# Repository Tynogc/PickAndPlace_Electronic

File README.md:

# PickAndPlace_Electronic
The Electronic-Side of an automatic SMT Pick&amp;Place-System

Programm: KiCad

Leiterplatten und embedded-Software für den Pick&Place Automaten

zur Verwendung dieses Repos sind noch die folgenden Repositorys nötig:
https://github.com/Virtex7/PhilippsKicadBauteile
https://github.com/ep092/library_toni.pretty

Diese enthalten KiCAD-Bauteile und Schaltplansymbole

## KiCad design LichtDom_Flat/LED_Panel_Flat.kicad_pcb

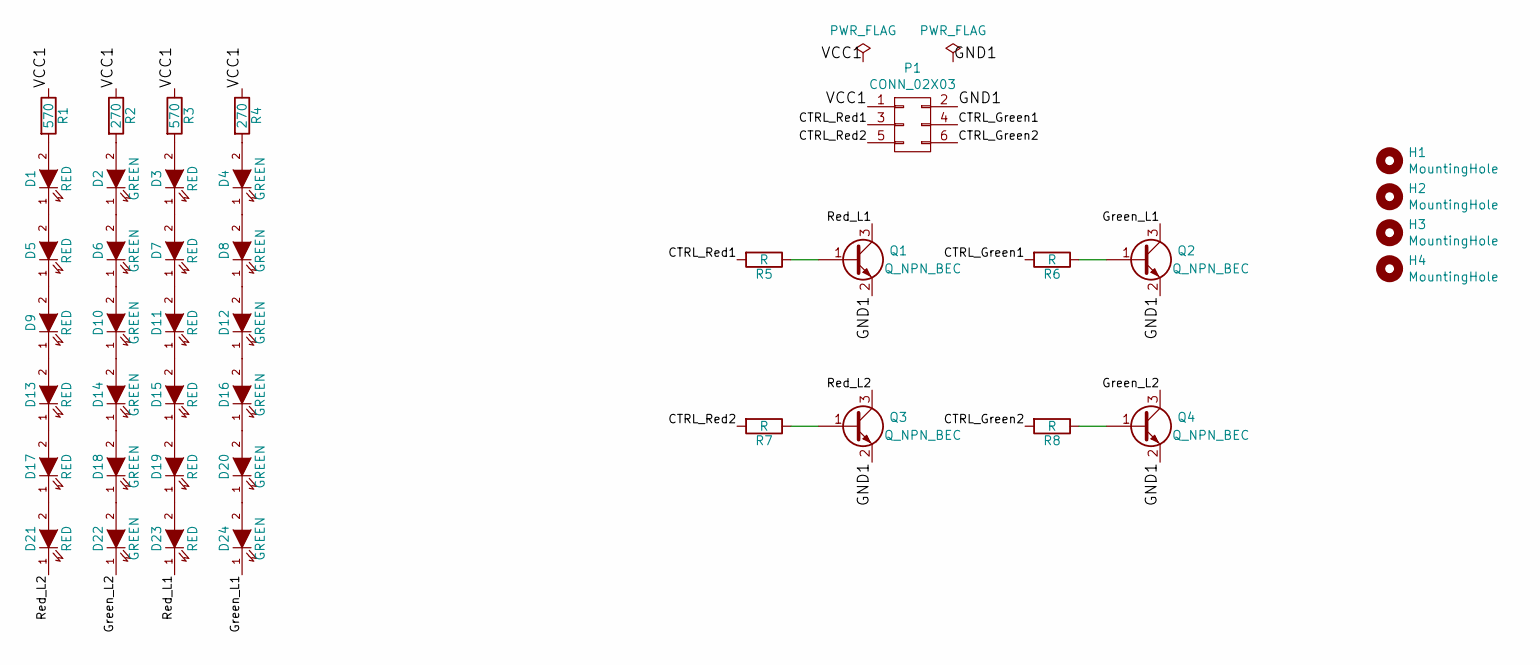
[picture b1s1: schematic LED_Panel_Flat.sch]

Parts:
D1, D3, D5, D7, D9, D11, D13, D15, D17, D19, D21, D23: RED; LED_PLCC-2
D2, D4, D6, D8, D10, D12, D14, D16, D18, D20, D22, D24: GREEN; LED_PLCC-2
H1, H2, H3, H4: MountingHole; MountingHole_3.2mm_M3_DIN965_Pad
P1: CONN_02X03; micro_match3x2
Q1, Q2, Q3, Q4: Q_NPN_BEC; SOT-23
R1, R3: 570; R_1206
R2, R4: 270; R_0805
R5, R6, R7, R8: R; R_0805

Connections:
/CTRL_Green1: P1.4, R6.2
/CTRL_Green2: P1.6, R8.2
/CTRL_Red1: P1.3, R5.2
/CTRL_Red2: P1.5, R7.2
/GND1: P1.2, Q1.2 (E), Q2.2 (E), Q3.2 (E), Q4.2 (E)
/Green_L1: D24.1 (K), Q2.3 (C)
/Green_L2: D22.1 (K), Q4.3 (C)
/Red_L1: D23.1 (K), Q1.3 (C)
/Red_L2: D21.1 (K), Q3.3 (C)
/VCC1: P1.1, R1.1, R2.1, R3.1, R4.1
unnamed: D1.2 (A), R1.2
unnamed: D2.2 (A), R2.2
unnamed: D3.2 (A), R3.2
unnamed: D4.2 (A), R4.2
unnamed: D5.1 (K), D9.2 (A)
unnamed: D1.1 (K), D5.2 (A)
unnamed: D6.1 (K), D10.2 (A)
unnamed: D2.1 (K), D6.2 (A)
unnamed: D7.1 (K), D11.2 (A)
unnamed: D3.1 (K), D7.2 (A)
unnamed: D8.1 (K), D12.2 (A)
unnamed: D4.1 (K), D8.2 (A)
unnamed: D9.1 (K), D13.2 (A)
unnamed: D10.1 (K), D14.2 (A)
unnamed: D11.1 (K), D15.2 (A)
unnamed: D12.1 (K), D16.2 (A)
unnamed: D13.1 (K), D17.2 (A)
unnamed: D14.1 (K), D18.2 (A)
unnamed: D15.1 (K), D19.2 (A)
unnamed: D16.1 (K), D20.2 (A)
unnamed: D17.1 (K), D21.2 (A)
unnamed: D18.1 (K), D22.2 (A)
unnamed: D19.1 (K), D23.2 (A)
unnamed: D20.1 (K), D24.2 (A)
unnamed: Q1.1 (B), R5.1
unnamed: Q2.1 (B), R6.1
unnamed: Q3.1 (B), R7.1
unnamed: Q4.1 (B), R8.1

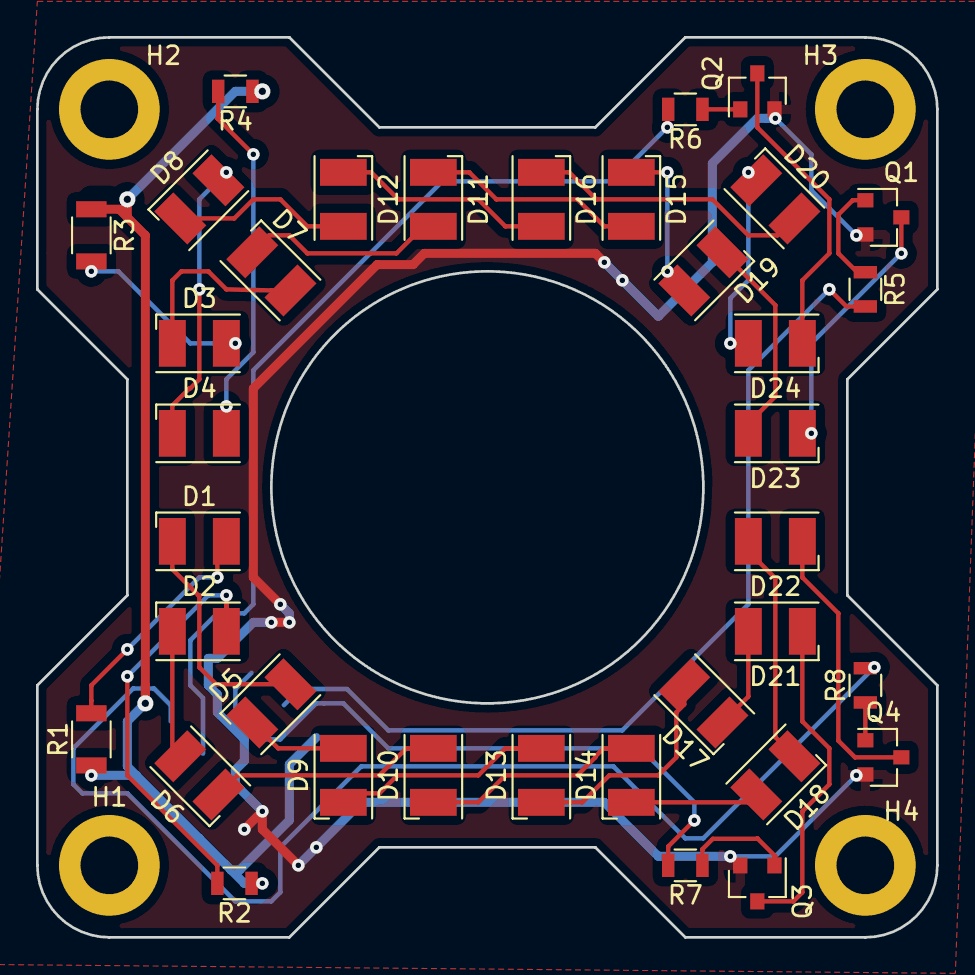
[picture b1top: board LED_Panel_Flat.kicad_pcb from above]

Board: 2 copper layers, 50.0 x 50.0 mm, 41 parts (1 on the bottom side), 38 nets.

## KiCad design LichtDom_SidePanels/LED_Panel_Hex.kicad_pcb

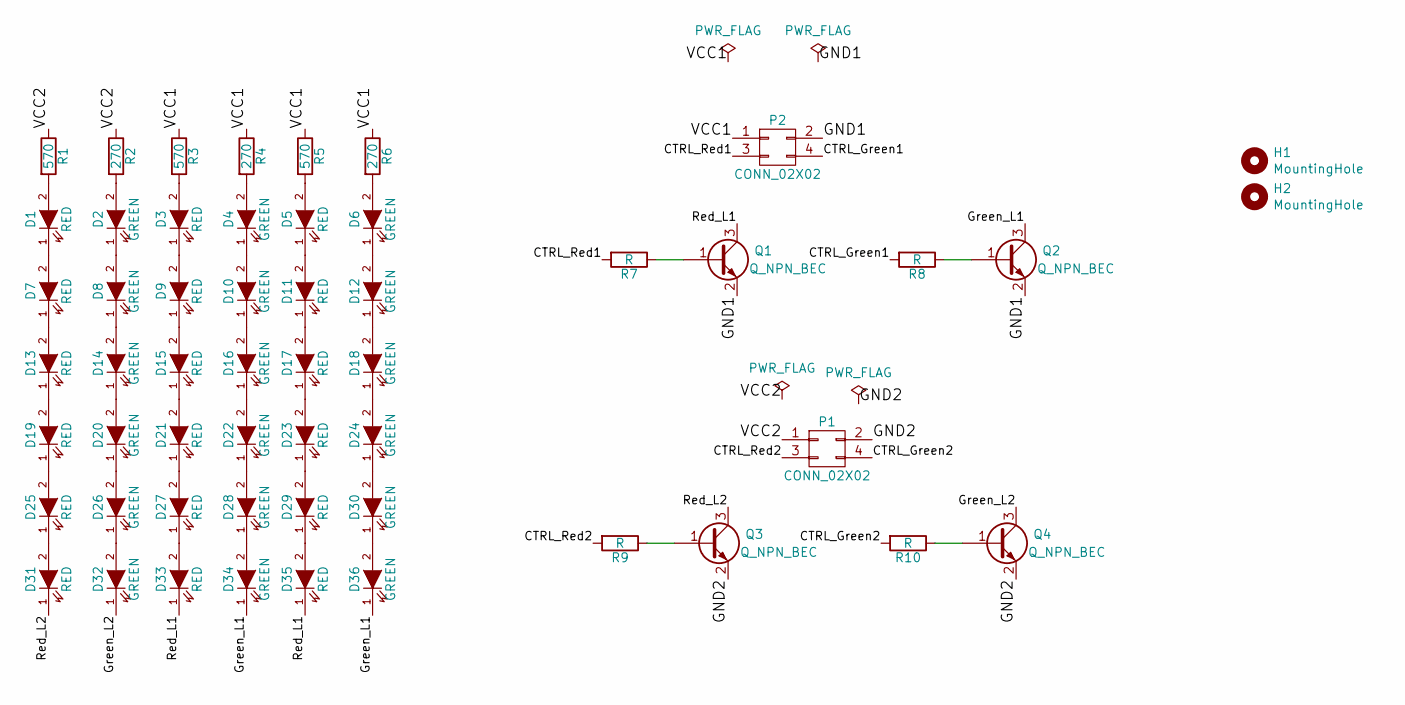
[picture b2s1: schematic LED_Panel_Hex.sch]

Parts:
D1, D3, D5, D7, D9, D11, D13, D15, D17, D19, D21, D23, D25, D27, D29, D31, D33, D35: RED; LED_PLCC-2
D2, D4, D6, D8, D10, D12, D14, D16, D18, D20, D22, D24, D26, D28, D30, D32, D34, D36: GREEN; LED_PLCC-2
H1, H2: MountingHole; MountingHole_3.2mm_M3_DIN965_Pad
P1, P2: CONN_02X02; micro_match3x2
Q1, Q2, Q3, Q4: Q_NPN_BEC; SOT-23
R1, R3, R5: 570; R_1206
R2, R4, R6: 270; R_0805
R7, R8, R9, R10: R; R_0805

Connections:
/CTRL_Green1: P2.4, R8.2
/CTRL_Green2: P1.4, R10.2
/CTRL_Red1: P2.3, R7.2
/CTRL_Red2: P1.3, R9.2
/GND1: P2.2, Q1.2 (E), Q2.2 (E)
/GND2: P1.2, Q3.2 (E), Q4.2 (E)
/Green_L1: D34.1 (K), D36.1 (K), Q2.3 (C)
/Green_L2: D32.1 (K), Q4.3 (C)
/Red_L1: D33.1 (K), D35.1 (K), Q1.3 (C)
/Red_L2: D31.1 (K), Q3.3 (C)
/VCC1: P2.1, R3.1, R4.1, R5.1, R6.1
/VCC2: P1.1, R1.1, R2.1
unnamed: D1.1 (K), D7.2 (A)
unnamed: D1.2 (A), R1.2
unnamed: D2.1 (K), D8.2 (A)
unnamed: D2.2 (A), R2.2
unnamed: D3.1 (K), D9.2 (A)
unnamed: D3.2 (A), R3.2
unnamed: D4.2 (A), R4.2
unnamed: D5.2 (A), R5.2
unnamed: D6.2 (A), R6.2
unnamed: D10.1 (K), D16.2 (A)
unnamed: D4.1 (K), D10.2 (A)
unnamed: D11.1 (K), D17.2 (A)
unnamed: D5.1 (K), D11.2 (A)
unnamed: D12.1 (K), D18.2 (A)
unnamed: D6.1 (K), D12.2 (A)
unnamed: D13.1 (K), D19.2 (A)
unnamed: D7.1 (K), D13.2 (A)
unnamed: D14.1 (K), D20.2 (A)
unnamed: D8.1 (K), D14.2 (A)
unnamed: D15.1 (K), D21.2 (A)
unnamed: D9.1 (K), D15.2 (A)
unnamed: D16.1 (K), D22.2 (A)
unnamed: D17.1 (K), D23.2 (A)
unnamed: D18.1 (K), D24.2 (A)
unnamed: D19.1 (K), D25.2 (A)
unnamed: D20.1 (K), D26.2 (A)
unnamed: D21.1 (K), D27.2 (A)
unnamed: D22.1 (K), D28.2 (A)
unnamed: D23.1 (K), D29.2 (A)
unnamed: D24.1 (K), D30.2 (A)
unnamed: D25.1 (K), D31.2 (A)
unnamed: D26.1 (K), D32.2 (A)
unnamed: D27.1 (K), D33.2 (A)
unnamed: D28.1 (K), D34.2 (A)
unnamed: D29.1 (K), D35.2 (A)
unnamed: D30.1 (K), D36.2 (A)
unnamed: Q1.1 (B), R7.1
unnamed: Q2.1 (B), R8.1
unnamed: Q3.1 (B), R9.1
unnamed: Q4.1 (B), R10.1

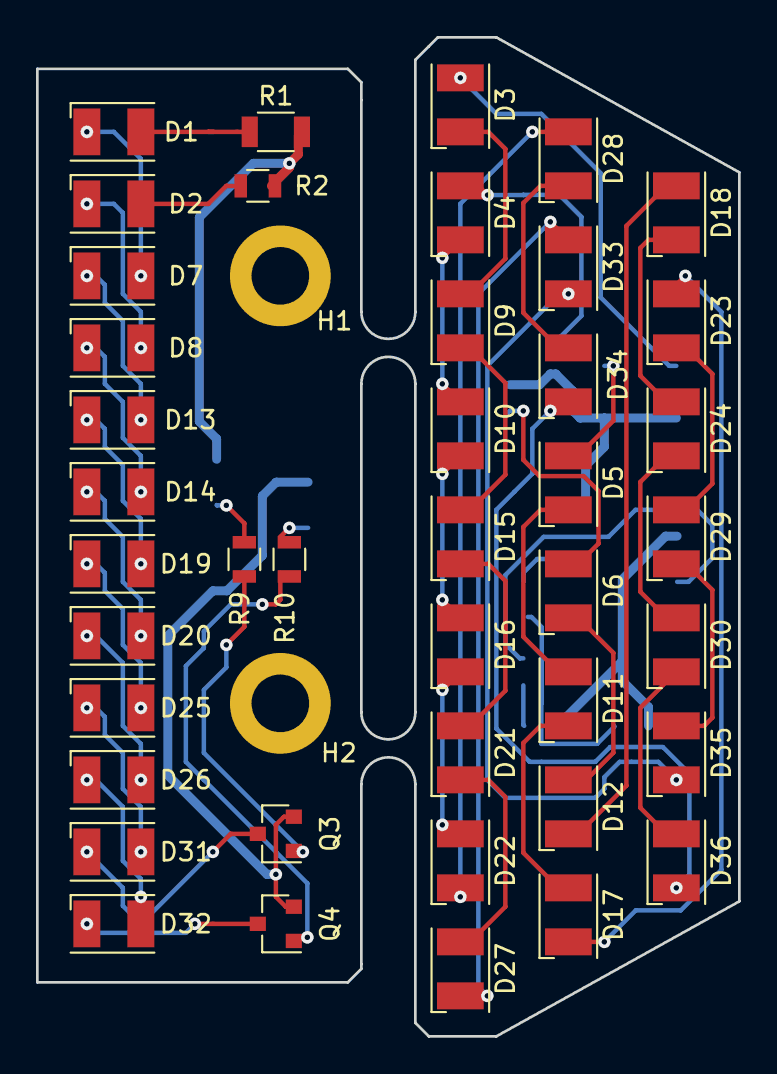
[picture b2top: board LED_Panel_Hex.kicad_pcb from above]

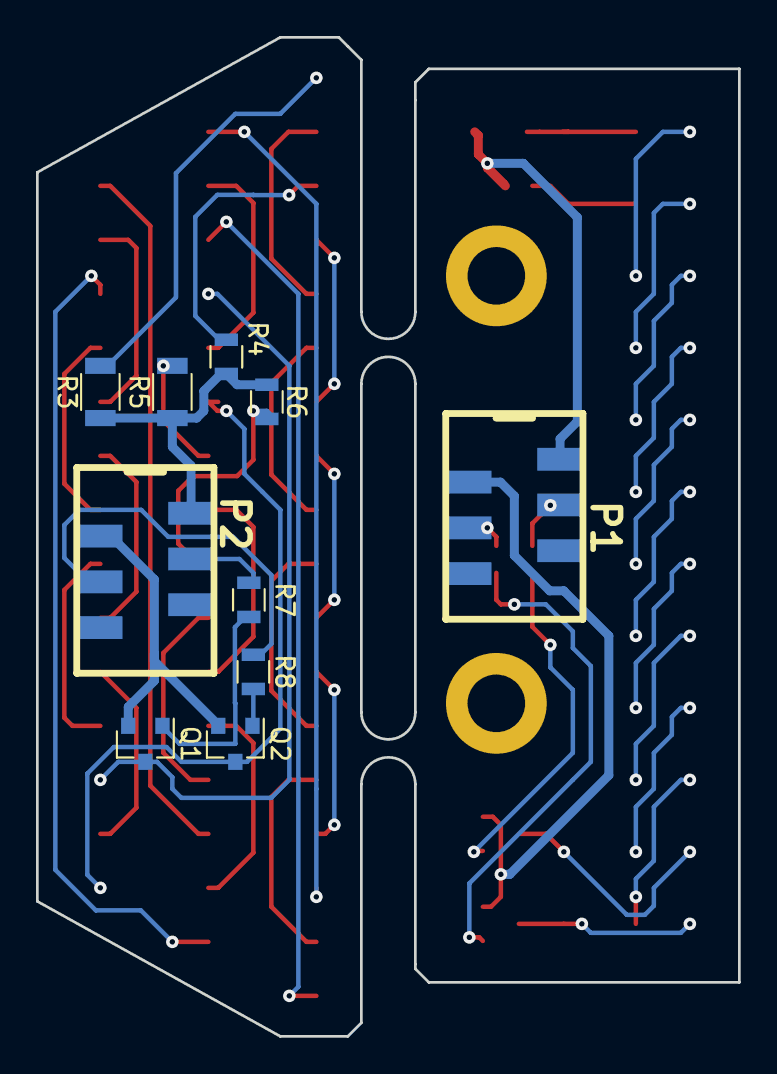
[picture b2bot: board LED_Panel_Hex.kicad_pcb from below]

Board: 2 copper layers, 39.0 x 55.5 mm, 54 parts (10 on the bottom side), 52 nets.

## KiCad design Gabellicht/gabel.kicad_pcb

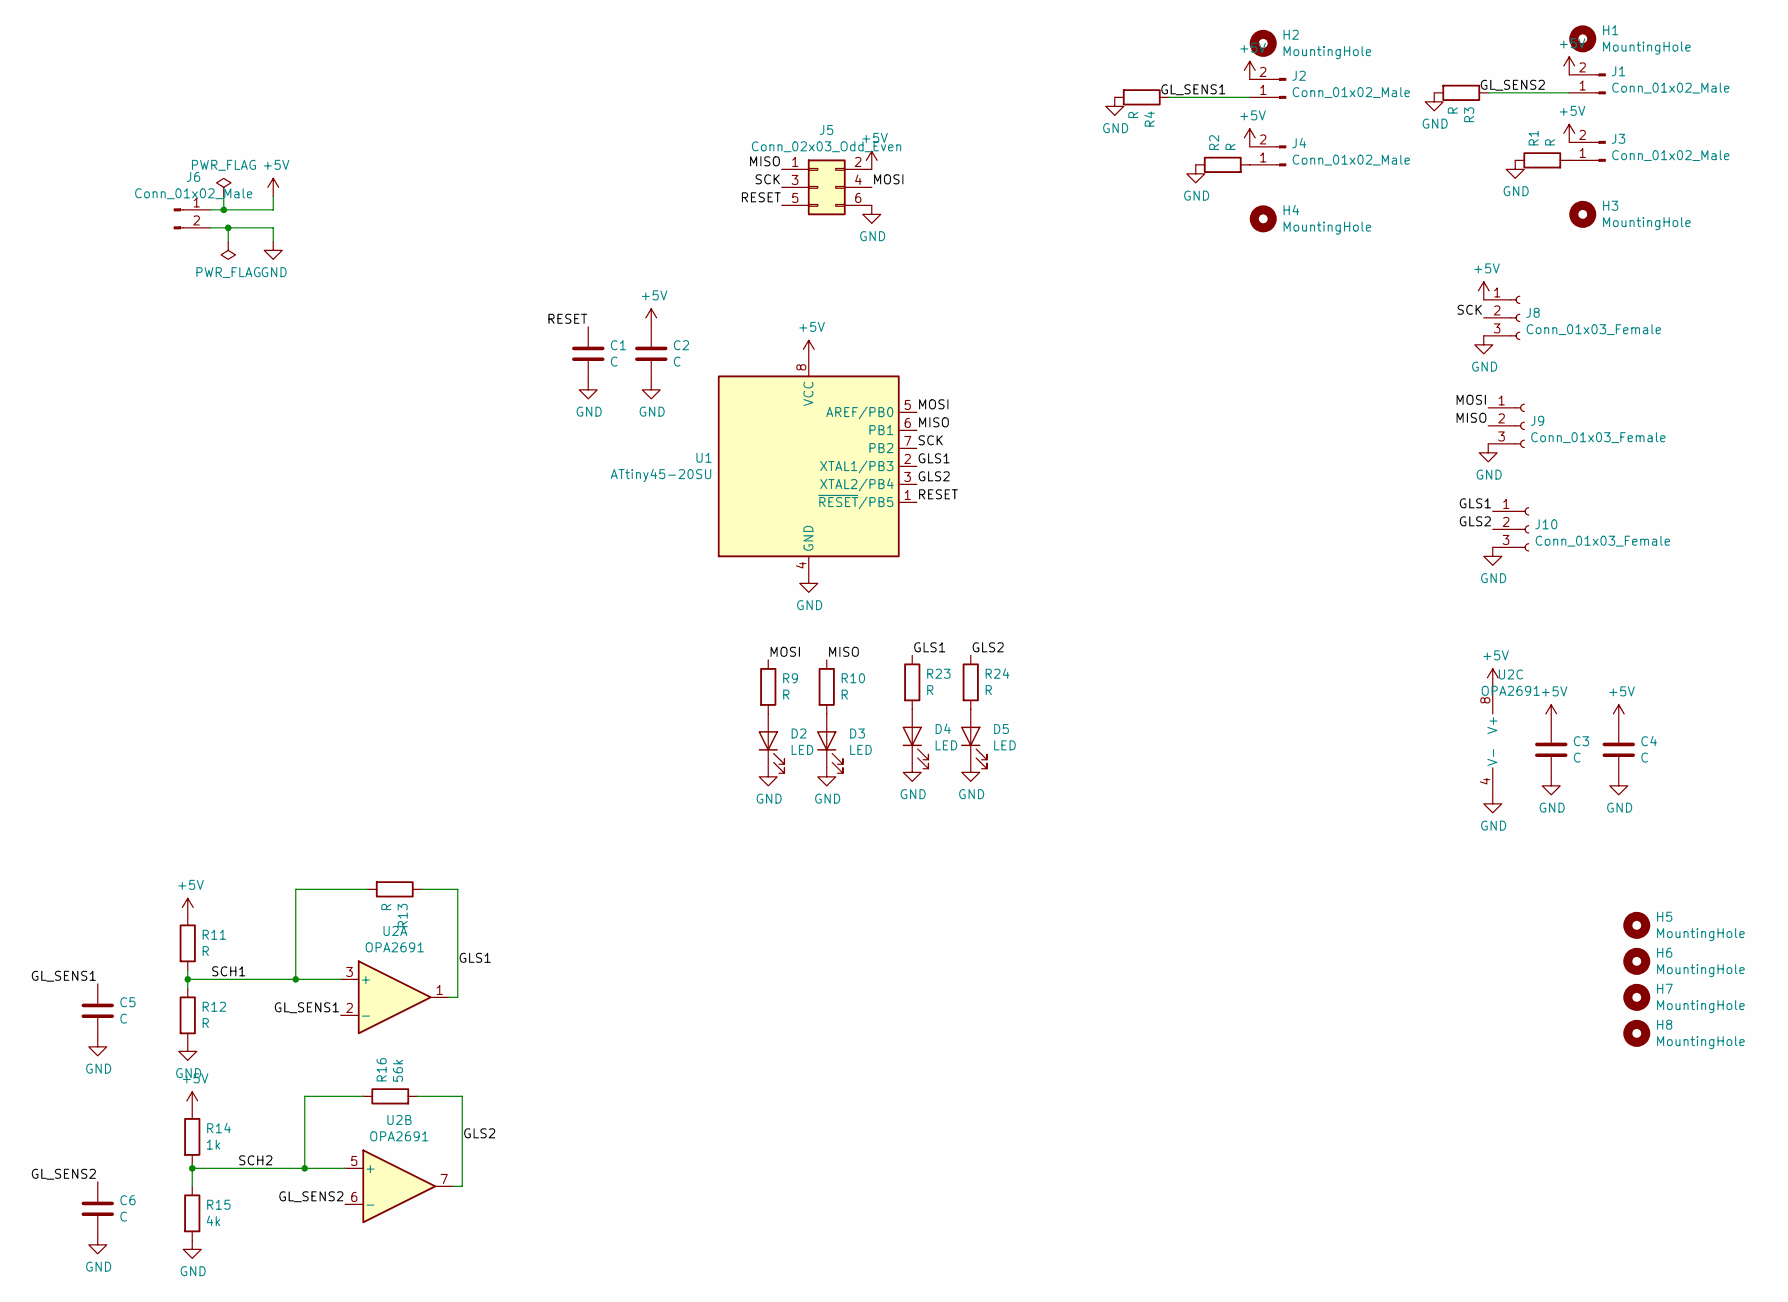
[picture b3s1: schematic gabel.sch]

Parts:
C1, C2, C3, C5, C6: C; C_0805
C4: C; C_1812
D2, D3: LED; LED_0805
D4, D5: LED; LED_D3.0mm_FlatTop
H1, H2, H3, H4: MountingHole; MountingHole_3.2mm_M3_DIN965_Pad
H5, H6, H7, H8: MountingHole; MountingHole_3.2mm_M3
J1, J2, J3, J4, J6: Conn_01x02_Male; Socket_Strip_Straight_1x02_Pitch2.54mm
J5: Conn_02x03_Odd_Even; Socket_Strip_Straight_2x03_Pitch2.54mm
J8, J9, J10: Conn_01x03_Female; Socket_Strip_Straight_1x03_Pitch2.54mm
R1, R2, R3, R4, R9, R10, R11, R12, R13, R23, R24: R; R_0805
R14: 1k; R_0805
R15: 4k; R_0805
R16: 56k; R_0805
U1: ATtiny45-20SU; TI_SO-PowerPAD-8
U2: OPA2691; TI_SO-PowerPAD-8

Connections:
+5V: C2.1, C3.1, C4.1, J1.2, J2.2, J3.2, J4.2, J5.2, J6.1, J8.1, R11.1, R14.1, U1.8 (VCC), U2.8 (V+)
/GLS1: J10.1, R13.1, R23.1, U1.2 (XTAL1/PB3), U2.1
/GLS2: J10.2, R16.2, R24.1, U1.3 (XTAL2/PB4), U2.7
/GL_SENS1: C5.1, J2.1, R4.1, U2.2 (-)
/GL_SENS2: C6.1, J1.1, R3.1, U2.6 (-)
/MISO: J5.1, J9.2, R10.1, U1.6 (PB1)
/MOSI: J5.4, J9.1, R9.1, U1.5 (AREF/PB0)
/RESET: C1.1, J5.5, U1.1 (~RESET~/PB5)
/SCH1: R11.2, R12.1, R13.2, U2.3 (+)
/SCH2: R14.2, R15.1, R16.1, U2.5 (+)
/SCK: J5.3, J8.2, U1.7 (PB2)
GND: C1.2, C2.2, C3.2, C4.2, C5.2, C6.2, D2.1 (K), D3.1 (K), D4.1 (K), D5.1 (K), J5.6, J6.2, J8.3, J9.3, J10.3, R1.1, R2.1, R3.2, R4.2, R12.2, R15.2, U1.4 (GND), U2.4 (V-)
unnamed: D2.2 (A), R9.2
unnamed: D3.2 (A), R10.2
unnamed: D4.2 (A), R23.2
unnamed: D5.2 (A), R24.2
unnamed: J3.1, R1.2
unnamed: J4.1, R2.2

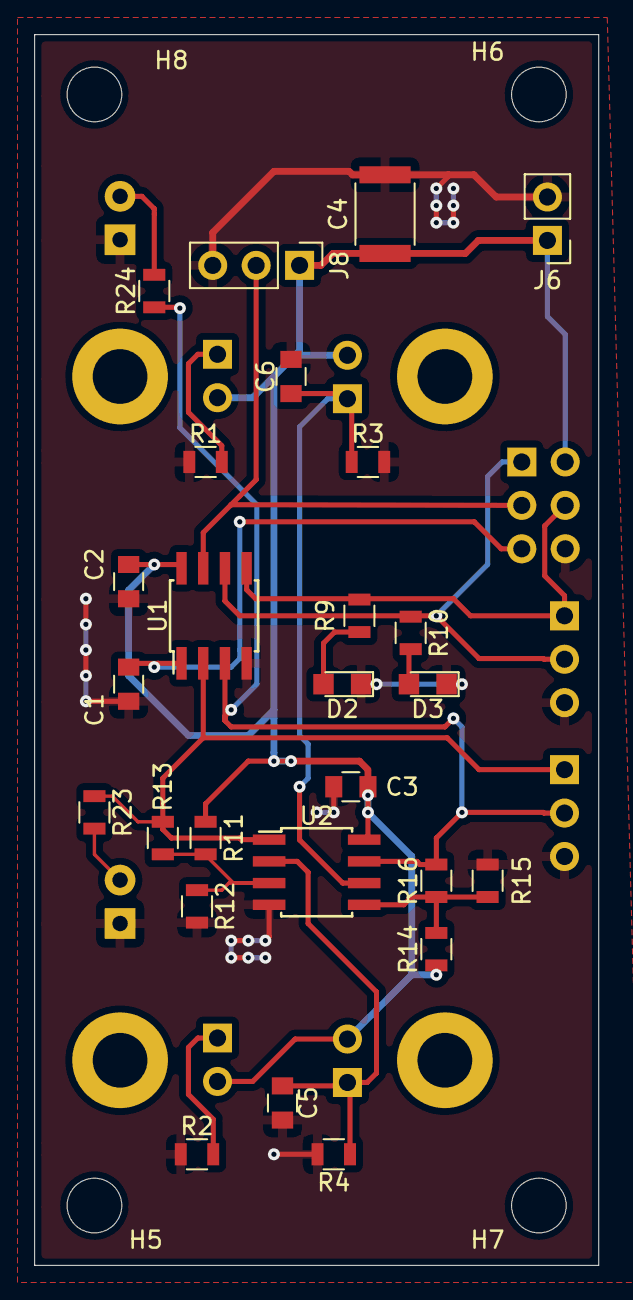
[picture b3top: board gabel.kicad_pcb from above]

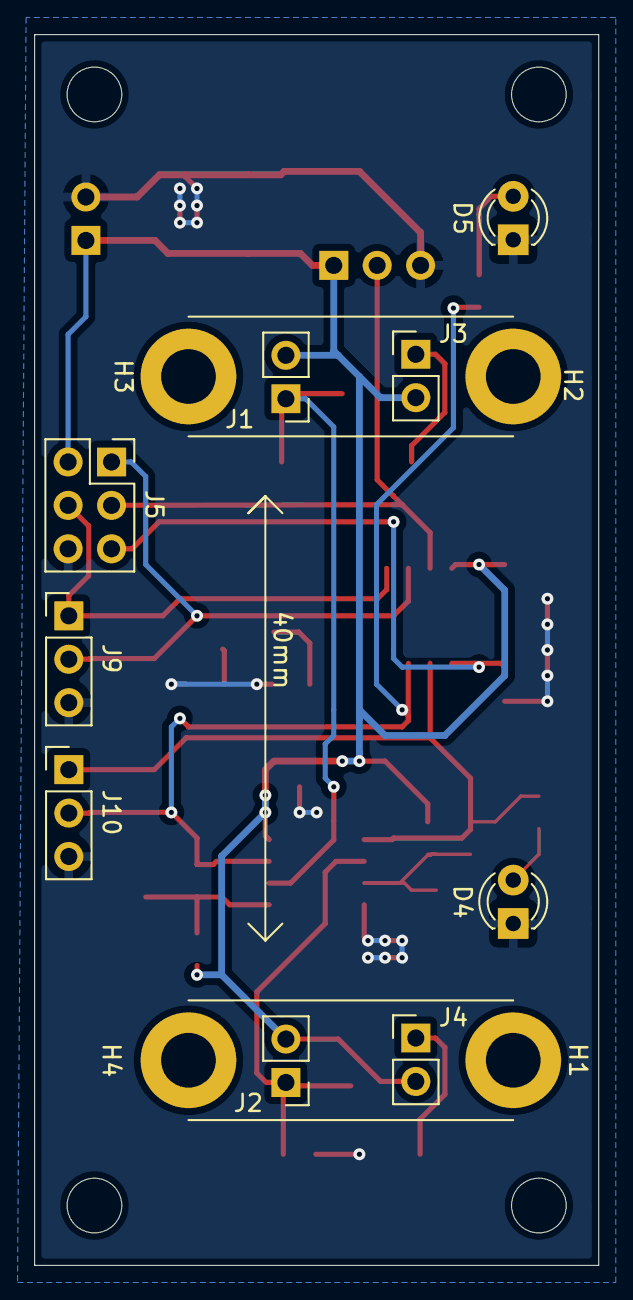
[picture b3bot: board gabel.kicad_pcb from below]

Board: 2 copper layers, 33.0 x 72.0 mm, 43 parts (13 on the bottom side), 18 nets.

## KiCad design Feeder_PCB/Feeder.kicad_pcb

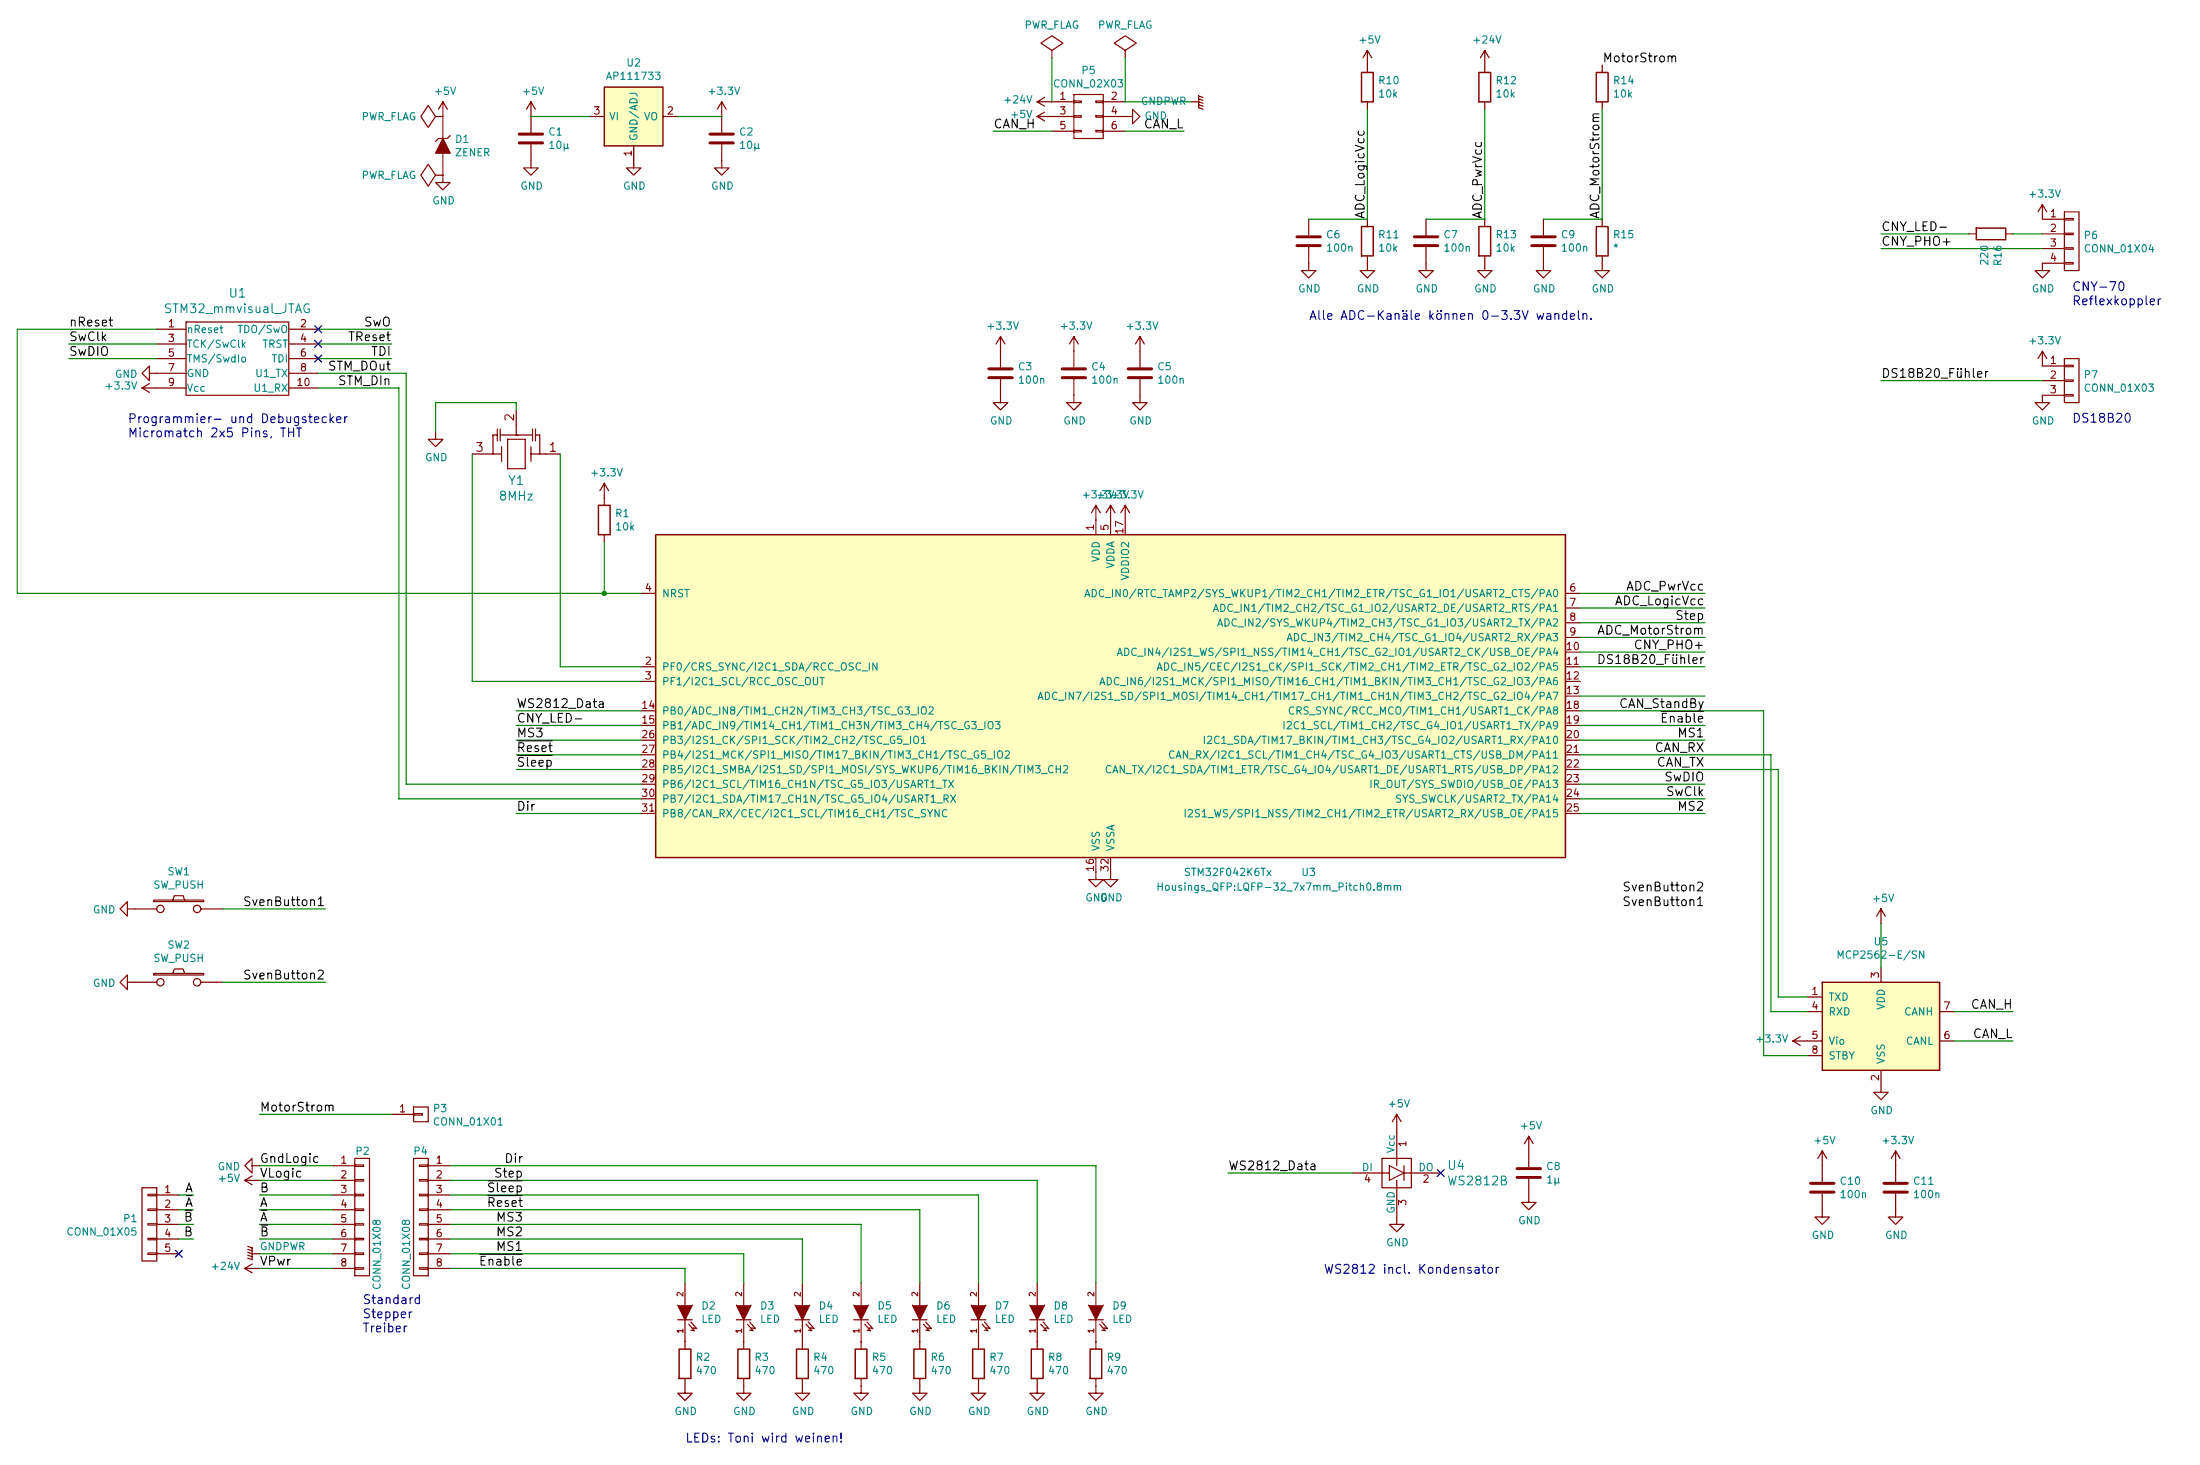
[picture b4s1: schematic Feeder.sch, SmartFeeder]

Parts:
C1, C2: 10µ; C_0805
C3, C4, C5, C6, C7, C9, C10, C11: 100n; C_0603
C8: 1µ; C_0603
D1: ZENER; D_MiniMELF_Standard
D2, D3, D4, D5, D6, D7, D8, D9: LED; LED_0603
P1: CONN_01X05; JST_XH_B05B-XH-A_05x2.50mm_Straight
P2, P4: CONN_01X08; Socket_Strip_Straight_1x08_Pitch2.54mm
P3: CONN_01X01; Pin_Header_Straight_1x01_Pitch2.54mm
P5: CONN_02X03; Pin_Header_Angled_2x03_Pitch2.54mm
P6: CONN_01X04; JST_PH_B4B-PH-K_04x2.00mm_Straight
P7: CONN_01X03; Pin_Header_Straight_1x03_Pitch2.54mm
R1, R10, R11, R12, R13, R14: 10k; R_0603
R2, R3, R4, R5, R6, R7, R8, R9: 470; R_0603
R15: *; R_0603
R16: 220; R_0603
SW1, SW2: SW_PUSH
U1: STM32_mmvisual_JTAG; MICROMATCH-10
U2: AP111733; SOT-223
U3: STM32F042K6Tx; LQFP-32_7x7mm_Pitch0.8mm
U4: WS2812B; LED_WS2812B-PLCC4
U5: MCP2562-E/SN; SOIC-8_3.9x4.9mm_Pitch1.27mm
Y1: 8MHz; CSTCE_3,2x1,3

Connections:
+3V3: C2.1, C3.1, C4.1, C5.1, C11.1, P6.1, P7.1, R1.1, U1.9 (Vcc), U2.2 (VO), U2.4 (VO), U3.1 (VDD), U3.5 (VDDA), U3.17 (VDDIO2), U5.5 (Vio)
+5V: C1.1, C8.1, C10.1, D1.1 (K), P2.2, P5.3, R10.1, U2.3 (VI), U4.1 (Vcc), U5.3 (VDD)
+24V: P2.8, P5.1, R12.1
/A: P1.1, P2.4
/ADC_LogicVcc: C6.1, R10.2, R11.1, U3.7 (ADC_IN1/TIM2_CH2/TSC_G1_IO2/USART2_DE/U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)
/ADC_MotorStrom: C9.1, R14.2, R15.1, U3.9 (ADC_IN3/TIM2_CH4/TSC_G1_IO4/USART2_RX/P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)
/ADC_PwrVcc: C7.1, R12.2, R13.1, U3.6 (ADC_IN0/RTC_TAMP2/SYS_WKUP1/TIM2_CH1/TI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)
/B: P1.4, P2.3
/CAN_H: P5.5, U5.7 (CANH)
/CAN_L: P5.6, U5.6 (CANL)
/CAN_RX: U3.21 (CAN_RX/I2C1_SCL/TIM1_CH4/TSC_G4_IO3/USA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), U5.4 (RXD)
/CAN_StandBy: U3.18 (CRS_SYNC/RCC_MCO/TIM1_CH1/USART1_CK/PA8), U5.8 (STBY)
/CAN_TX: U3.22 (CAN_TX/I2C1_SDA/TIM1_ETR/TSC_G4_IO4/USA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), U5.1 (TXD)
/CNY_LED-: R16.2, U3.15 (PB1/ADC_IN9/TIM14_CH1/TIM1_CH3N/TIM3_CH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)
/CNY_PHO+: P6.3, U3.10 (ADC_IN4/I2S1_WS/SPI1_NSS/TIM14_CH1/TSC_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)
/DS18B20_Fühler: P7.2, U3.11 (ADC_IN5/CEC/I2S1_CK/SPI1_SCK/TIM2_CH1/T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)
/Dir: D9.2 (A), P4.1, U3.31 (PB8/CAN_RX/CEC/I2C1_SCL/TIM16_CH1/TSC_S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)
/MS1: D3.2 (A), P4.7, U3.20 (I2C1_SDA/TIM17_BKIN/TIM1_CH3/TSC_G4_IO2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)
/MS2: D4.2 (A), P4.6, U3.25 (I2S1_WS/SPI1_NSS/TIM2_CH1/TIM2_ETR/USAR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)
/MS3: D5.2 (A), P4.5, U3.26 (PB3/I2S1_CK/SPI1_SCK/TIM2_CH2/TSC_G5_IO1)
/MotorStrom: P3.1, R14.1
/STM_DIn: U1.10 (U1_RX), U3.30 (PB7/I2C1_SDA/TIM17_CH1N/TSC_G5_IO4/USAR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)
/STM_DOut: U1.8 (U1_TX), U3.29 (PB6/I2C1_SCL/TIM16_CH1N/TSC_G5_IO3/USAR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)
/Step: D8.2 (A), P4.2, U3.8 (ADC_IN2/SYS_WKUP4/TIM2_CH3/TSC_G1_IO3/U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)
/SwClk: U1.3 (TCK/SwClk), U3.24 (SYS_SWCLK/USART2_TX/PA14)
/SwDIO: U1.5 (TMS/SwdIo), U3.23 (IR_OUT/SYS_SWDIO/USB_OE/PA13)
/SwO: U1.2 (TDO/SwO)
/TDI: U1.6 (TDI)
/TReset: U1.4 (TRST)
/WS2812_Data: U3.14 (PB0/ADC_IN8/TIM1_CH2N/TIM3_CH3/TSC_G3_I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), U4.4 (DI)
/nReset: R1.2, U1.1 (nReset), U3.4 (NRST)
/~A: P1.2, P2.5
/~B: P1.3, P2.6
/~Enable: D2.2 (A), P4.8, U3.19 (I2C1_SCL/TIM1_CH2/TSC_G4_IO1/USART1_TX/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)
/~Reset: D6.2 (A), P4.4, U3.27 (PB4/I2S1_MCK/SPI1_MISO/TIM17_BKIN/TIM3_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)
/~Sleep: D7.2 (A), P4.3, U3.28 (PB5/I2C1_SMBA/I2S1_SD/SPI1_MOSI/SYS_WKU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)
GND: C1.2, C2.2, C3.2, C4.2, C5.2, C6.2, C7.2, C8.2, C9.2, C10.2, C11.2, D1.2 (A), P2.1, P5.4, P6.4, P7.3, R2.2, R3.2, R4.2, R5.2, R6.2, R7.2, R8.2, R9.2, R11.2, R13.2, R15.2, SW1.1, SW2.1, U1.7 (GND), U2.1 (GND/ADJ), U3.16 (VSS), U3.32 (VSSA), U4.3 (GND), U5.2 (VSS), Y1.2
GNDPWR: P2.7, P5.2
unnamed: D2.1 (K), R2.1
unnamed: D3.1 (K), R3.1
unnamed: D4.1 (K), R4.1
unnamed: D5.1 (K), R5.1
unnamed: D6.1 (K), R6.1
unnamed: D7.1 (K), R7.1
unnamed: D8.1 (K), R8.1
unnamed: D9.1 (K), R9.1
unnamed: P6.2, R16.1
unnamed: U3.2 (PF0/CRS_SYNC/I2C1_SDA/RCC_OSC_IN), Y1.1
unnamed: U3.3 (PF1/I2C1_SCL/RCC_OSC_OUT), Y1.3

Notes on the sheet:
Standard Stepper Treiber
Alle ADC-Kanäle können 0-3.3V wandeln.
Programmier- und Debugstecker Micromatch 2x5 Pins, THT
LEDs: Toni wird weinen!
WS2812 incl. Kondensator
CNY-70 Reflexkoppler
DS18B20

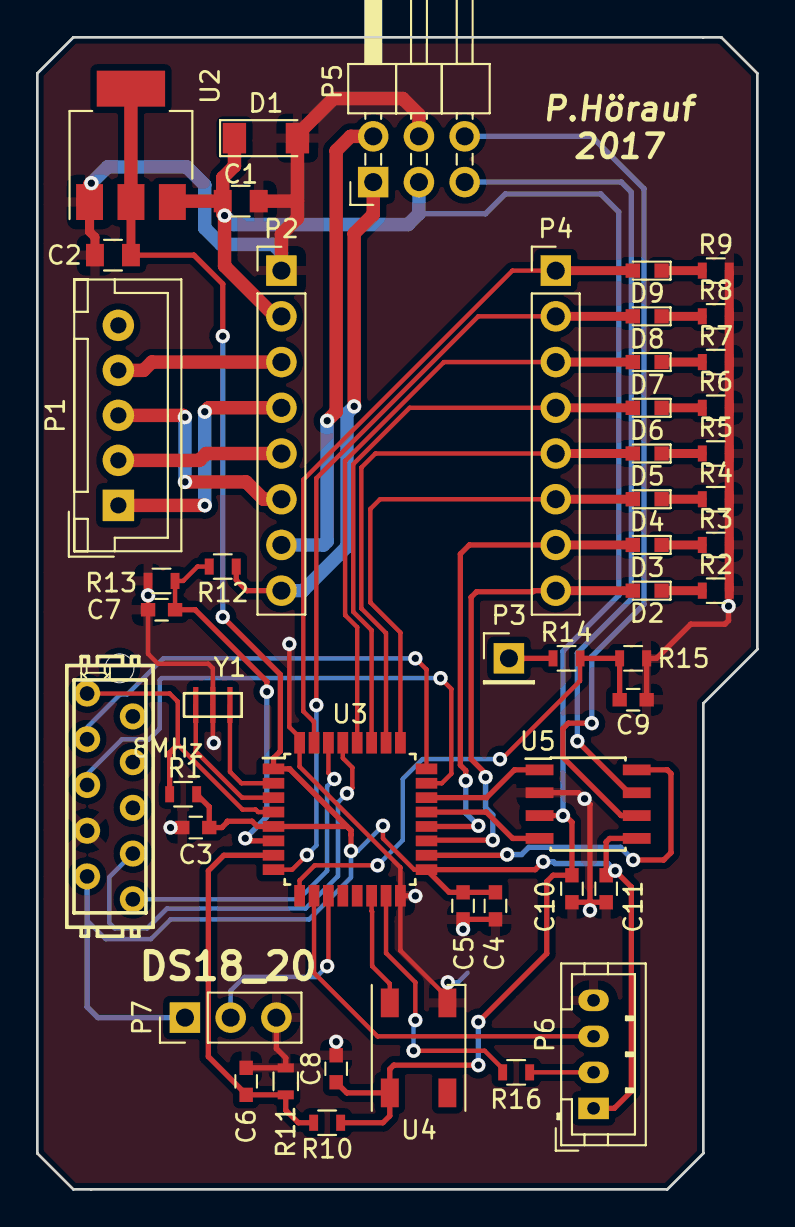
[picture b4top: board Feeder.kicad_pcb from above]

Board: 2 copper layers, 40.0 x 64.0 mm, 49 parts (0 on the bottom side), 46 nets.

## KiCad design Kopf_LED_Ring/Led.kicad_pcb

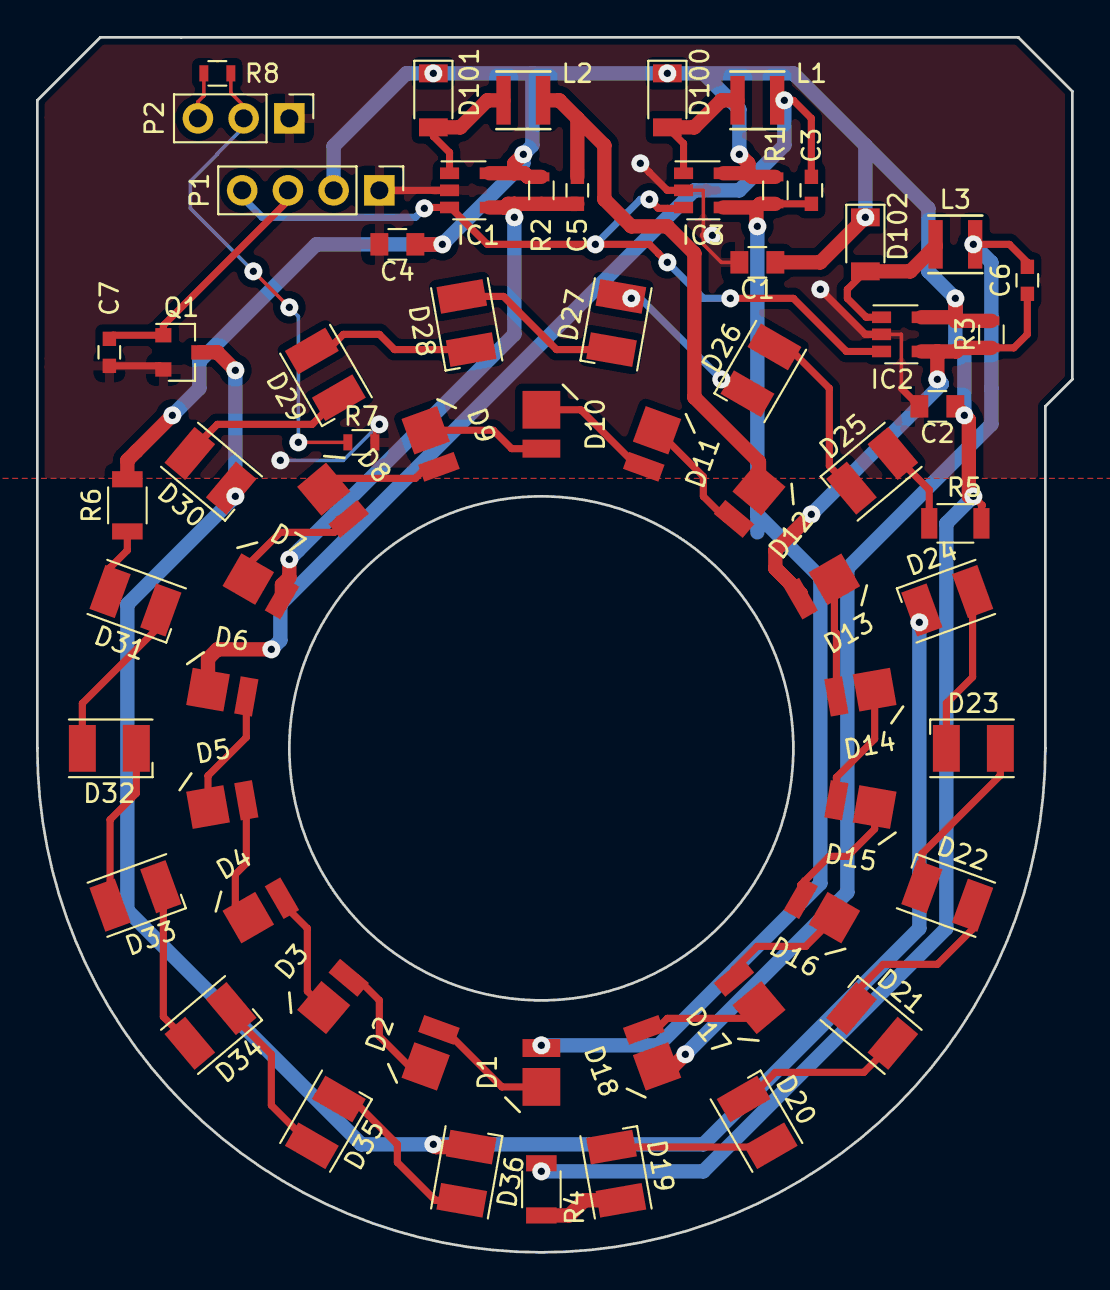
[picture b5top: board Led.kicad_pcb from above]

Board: 2 copper layers, 57.5 x 67.5 mm, 63 parts (0 on the bottom side), 49 nets.

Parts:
C1, C2, C4: 2u2; C_0805
C3, C5, C6, C7: 100n; C_0603
D1, D2, D3, D4, D5, D6, D7, D8, D9, D10, D11, D12, D13, D14, D15, D16, D17, D18: White; PLCC_EAHC2835
D19, D20, D21, D22, D23, D24, D25, D26, D27, D28, D29, D30, D31, D32, D33, D34, D35, D36: RED; LED_PLCC-2
D100, D101, D102: D_Schottky; D_1206
IC1, IC2, IC3: AL8808; SOT-23-5
L1, L2, L3: L; Inductor_Taiyo-Yuden_MD-3030
P1: CONN_01X04; Socket_Strip_Straight_1x04_Pitch2.54mm
P2: CONN_01X03; Socket_Strip_Straight_1x03_Pitch2.54mm
Q1: Q_NMOS_GSD; SOT-23
R1, R2, R3: 1R 1%; R_0603
R4, R5, R6: R; R_1206
R7: TempSens; R_0603
R8: R; R_0603

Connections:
+24V: C1.1, C2.1, C4.1, D100.1, D101.1, D102.1, IC1.5, IC2.5, IC3.5, P1.2, R1.2, R2.2, R3.2, R4.1, R5.1, R6.1
/CTRL_R: C7.1, P1.3, Q1.1
/CTRL_W: IC1.3, IC2.3, IC3.3, P1.4
/H1: C3.1, D1.2, IC3.4, R1.1
/H2: C5.1, D7.2, IC1.4, R2.1
/H3: C6.1, D13.2, IC2.4, R3.1
/L1: C3.2, D6.1, L1.1
/L2: C5.2, D12.1, L2.1
/L3: C6.2, D18.1, L3.1
/SW1: D100.2, IC3.1, L1.2
/SW2: D101.2, IC1.1, L2.2
/SW3: D102.2, IC2.1, L3.2
/TempSens: P2.2, R7.1, R8.2
/TempSensH: P2.3, R8.1
GND: C1.2, C2.2, C4.2, C7.2, IC1.2, IC2.2, IC3.2, P1.1, P2.1, Q1.2, R7.2
unnamed: D1.1, D2.2
unnamed: D2.1, D3.2
unnamed: D3.1, D4.2
unnamed: D4.1, D5.2
unnamed: D5.1, D6.2
unnamed: D7.1, D8.2
unnamed: D8.1, D9.2
unnamed: D10.1, D11.2
unnamed: D9.1, D10.2
unnamed: D11.1, D12.2
unnamed: D13.1, D14.2
unnamed: D14.1, D15.2
unnamed: D15.1, D16.2
unnamed: D16.1, D17.2
unnamed: D17.1, D18.2
unnamed: D19.1, D20.2
unnamed: D19.2, R4.2
unnamed: D20.1, D21.2
unnamed: D21.1, D22.2
unnamed: D22.1, D23.2
unnamed: D23.1, D24.2
unnamed: D24.1, D30.1, D36.1, Q1.3
unnamed: D25.1, D26.2
unnamed: D25.2, R5.2
unnamed: D26.1, D27.2
unnamed: D27.1, D28.2
unnamed: D28.1, D29.2
unnamed: D29.1, D30.2
unnamed: D31.1, D32.2
unnamed: D31.2, R6.2
unnamed: D32.1, D33.2
unnamed: D33.1, D34.2
unnamed: D34.1, D35.2
unnamed: D35.1, D36.2
